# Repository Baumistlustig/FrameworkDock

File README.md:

# FrameworkDock

A dock for the Framwork Laptop 13 which extends the capacity of Expansion Cards on the right side to 5

## Features

- 4 Expansion Cards (Work in Progress)
- [Minimal Small Input Module](https://github.com/FrameworkComputer/InputModules/tree/main/Electrical/MinimalSmallInputModule) (Planned)

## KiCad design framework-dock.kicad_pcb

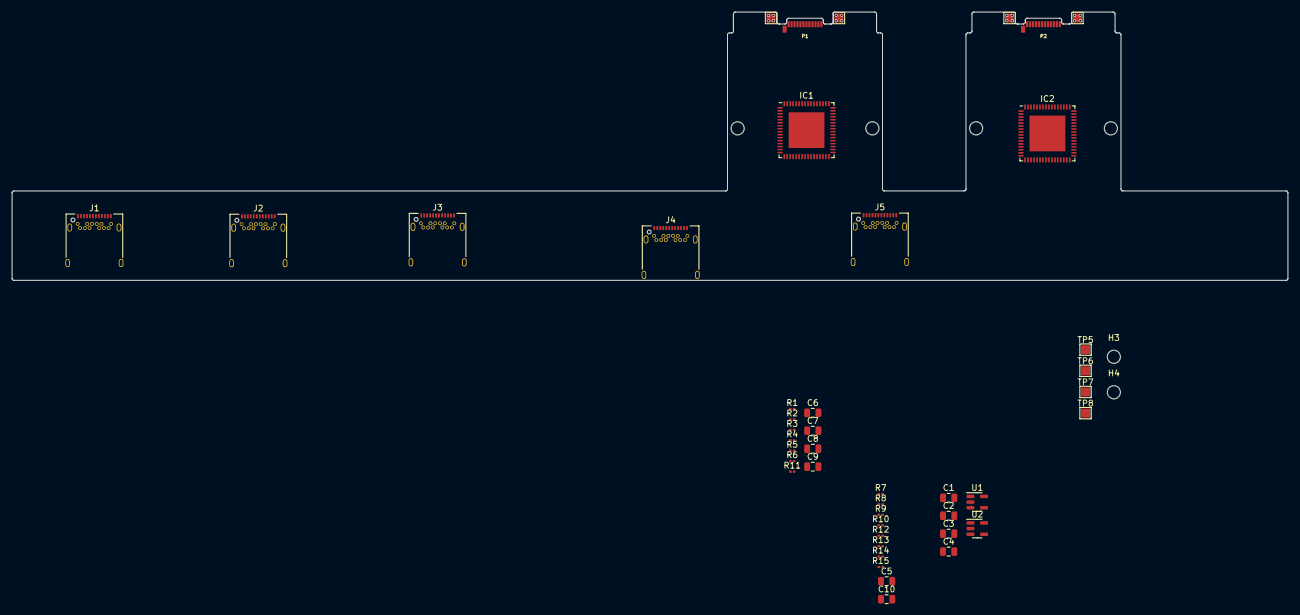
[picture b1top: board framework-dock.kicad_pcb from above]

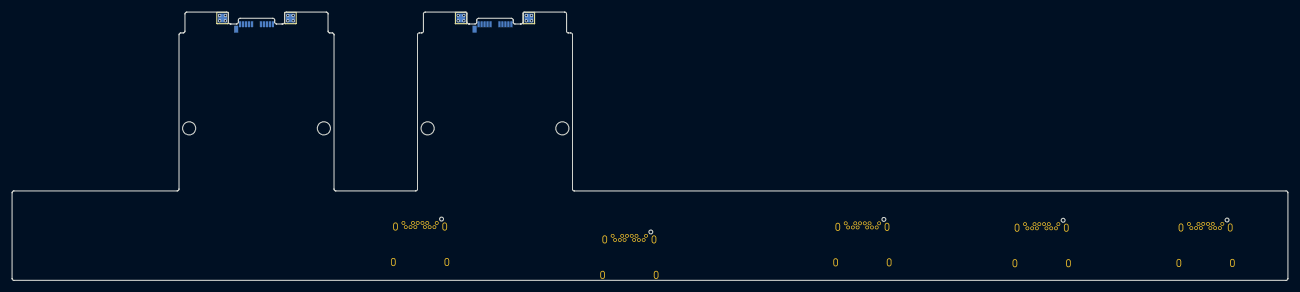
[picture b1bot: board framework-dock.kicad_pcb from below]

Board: 2 copper layers, 214.0 x 45.0 mm, 54 parts (4 on the bottom side), 20 nets, no tracks yet.

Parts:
C1, C2, C3, C4, C5, C10: 10uF; C_0805_2012Metric
C6, C7, C8, C9: 0.1uF; C_0805_2012Metric
H1, H2, H3, H3#2, H4, H4#2: MountingHole; MountingHole_2.2mm_M2
IC1, IC2: TUSB8042ARGCT; QFN-64-1EP_9x9mm_P0.5mm_EP6x6mm
J1, J2, J3, J4, J5: USB_C_Receptacle; USB_C_Receptacle_Amphenol_12401548E4-2A
P1, P2: USB_C_Plug; USB_C_Plug_Molex_105444
R1, R2, R3, R4, R5, R6, R11: 5.1k; R_0201_0603Metric
R7, R15: 90.9k; R_0201_0603Metric
R8, R14: 10k; R_0201_0603Metric
R9, R10, R12, R13: 4.7k; R_0201_0603Metric
TP1, TP2, TP3, TP4, TP5, TP5#2, TP6, TP6#2, TP7, TP7#2, TP8, TP8#2: TestPoint; TestPoint_Pad_1.5x1.5mm
U1: AP2112K-1.2; SOT-23-5
U2: AP2112K-3.3; SOT-23-5

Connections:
+1V2: C4.1, IC1.5 (VDD_1), IC1.8 (VDD_2), IC1.13 (VDD_3), IC1.21 (VDD_4), IC1.28 (VDD_5), IC1.31 (VDD_6), IC1.51 (VDD_7), IC1.57 (VDD_8), IC2.5 (VDD_1), IC2.8 (VDD_2), IC2.13 (VDD_3), IC2.21 (VDD_4), IC2.28 (VDD_5), IC2.31 (VDD_6), IC2.51 (VDD_7), IC2.57 (VDD_8), U1.5 (VOUT)
+3.3V: C2.1, IC1.16 (VDD33_1), IC1.34 (VDD33_2), IC1.52 (VDD33_3), IC1.63 (VDD33_4), IC2.16 (VDD33_1), IC2.34 (VDD33_2), IC2.52 (VDD33_3), IC2.63 (VDD33_4), U2.5 (VOUT)
GND: C1.2, C2.2, C3.2, C4.2, C5.2, C10.2, J1.A1 (GND), J1.A12 (GND), J1.B1 (GND), J1.B12 (GND), J1.S1 (SHIELD), J2.A1 (GND), J2.A12 (GND), J2.B1 (GND), J2.B12 (GND), J2.S1 (SHIELD), J3.A1 (GND), J3.A12 (GND), J3.B1 (GND), J3.B12 (GND), J3.S1 (SHIELD), J4.A1 (GND), J4.A12 (GND), J4.B1 (GND), J4.B12 (GND), J4.S1 (SHIELD), J5.A1 (GND), J5.A12 (GND), J5.B1 (GND), J5.B12 (GND), J5.S1 (SHIELD), P1.A1, P1.A12, P1.B1, P1.B12, P1.S1, P2.A1, P2.A12, P2.B1, P2.B12, P2.S1, R1.2, R2.2, R3.2, R4.2, R5.2, R6.2, R8.1, R9.2, R10.2, R11.2, R12.2, R13.2, R14.1, TP1.1, TP2.1, TP3.1, TP4.1, TP5.1, TP5#2.1, TP6.1, TP6#2.1, TP7.1, TP7#2.1, TP8.1, TP8#2.1, U1.2 (GND), U2.2 (GND)
unnamed: IC1.40 (FULLPWRMGMTZ/SMBA1/SS_UP), R10.1
unnamed: IC1.42 (GANGED/SMBA2/HS_UP), R9.1
unnamed: IC1.48 (USB_VBUS), R7.2, R8.2
unnamed: IC2.40 (FULLPWRMGMTZ/SMBA1/SS_UP), R13.1
unnamed: IC2.42 (GANGED/SMBA2/HS_UP), R12.1
unnamed: IC2.48 (USB_VBUS), R14.2, R15.2
unnamed: J1.A5 (CC1), R2.1
unnamed: J2.A5 (CC1), R3.1
unnamed: J3.A5 (CC1), R5.1
unnamed: J4.A5 (CC1), R4.1
unnamed: J5.A5 (CC1), R6.1
unnamed: P1.A5, P2.A5
TX1+: C7.1, C7.2, IC1.55 (USB_SSTXP_UP)
TX1-: C6.1, C6.2, IC1.56 (USB_SSTXM_UP), P1.A2
TX2+: C9.1, C9.2, IC2.55 (USB_SSTXP_UP)
TX2-: C8.1, C8.2, IC2.56 (USB_SSTXM_UP)
VBUS: C1.1, C3.1, C5.1, C10.1, J1.A4 (VBUS), J1.A9 (VBUS), J1.B4 (VBUS), J1.B9 (VBUS), J2.A4 (VBUS), J2.A9 (VBUS), J2.B4 (VBUS), J2.B9 (VBUS), J3.A4 (VBUS), J3.A9 (VBUS), J3.B4 (VBUS), J3.B9 (VBUS), J4.A4 (VBUS), J4.A9 (VBUS), J4.B4 (VBUS), J4.B9 (VBUS), J5.A4 (VBUS), J5.A9 (VBUS), J5.B4 (VBUS), J5.B9 (VBUS), P1.A4, P1.A9, P1.B4, P1.B9, P2.A4, P2.A9, P2.B4, P2.B9, R7.1, R15.1, U1.1 (VIN), U1.3 (EN), U2.1 (VIN), U2.3 (EN)

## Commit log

2023-04-29 Added README.md
2023-04-29 Added Basic PCB Outline
2023-04-29 Updated Basic PCB Outline
2023-04-30 Added Downstream 1
2023-04-30 Added Power
2023-04-30 Updated Basic Board Outline

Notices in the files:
framework-dock.kicad_pcb:
This work is licensed under a Creative Commons Attribution 4.0 International License
